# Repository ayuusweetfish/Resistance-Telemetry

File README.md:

# Resistance Telemetry

*🚧 Feature complete. Docs to be polished.*

A compact sensor for a variable resistance that transmits data through BLE. A client program provides an interface for plotting and inspecting values on a desktop computer.

The device is physically compact (3.3 cm × 1.7 cm, around the size of the battery cell plus the antenna). It is powered by a LIR2016 cell and requires no setup on the computer side. Resolution is 24-bit, but no extensive calibration has currently been carried out. Designed for laboratory use, e.g. for e-skin gloves user studies.

## Directory structure

- **hardware/**: Circuit board design files.
- **firmware/**: Firmware (PlatformIO / C).
- **client/**: The client in C++. A Windows build is automated through [GitHub Actions](https://github.com/ayuusweetfish/Resistance-Telemetry/actions).
- **misc/**: Miscellaneous files and backups.
  - **STM32F1_test1/**: Test BLE transmission on a [blue pill](https://stm32-base.org/boards/STM32F103C8T6-Blue-Pill.html) board.
  - **compress_24b.c**: Data compression through least-squares quadratic fitting. Not employed in the final version due to nonnecessity for further enhancement.

## Permit

All content in this repository is released under [CC BY-NC-SA 4.0](https://creativecommons.org/licenses/by-nc-sa/4.0/). Additionally, software source code is dual-licensed by [Hippocratic License 2.1](https://spdx.org/licenses/Hippocratic-2.1.html).

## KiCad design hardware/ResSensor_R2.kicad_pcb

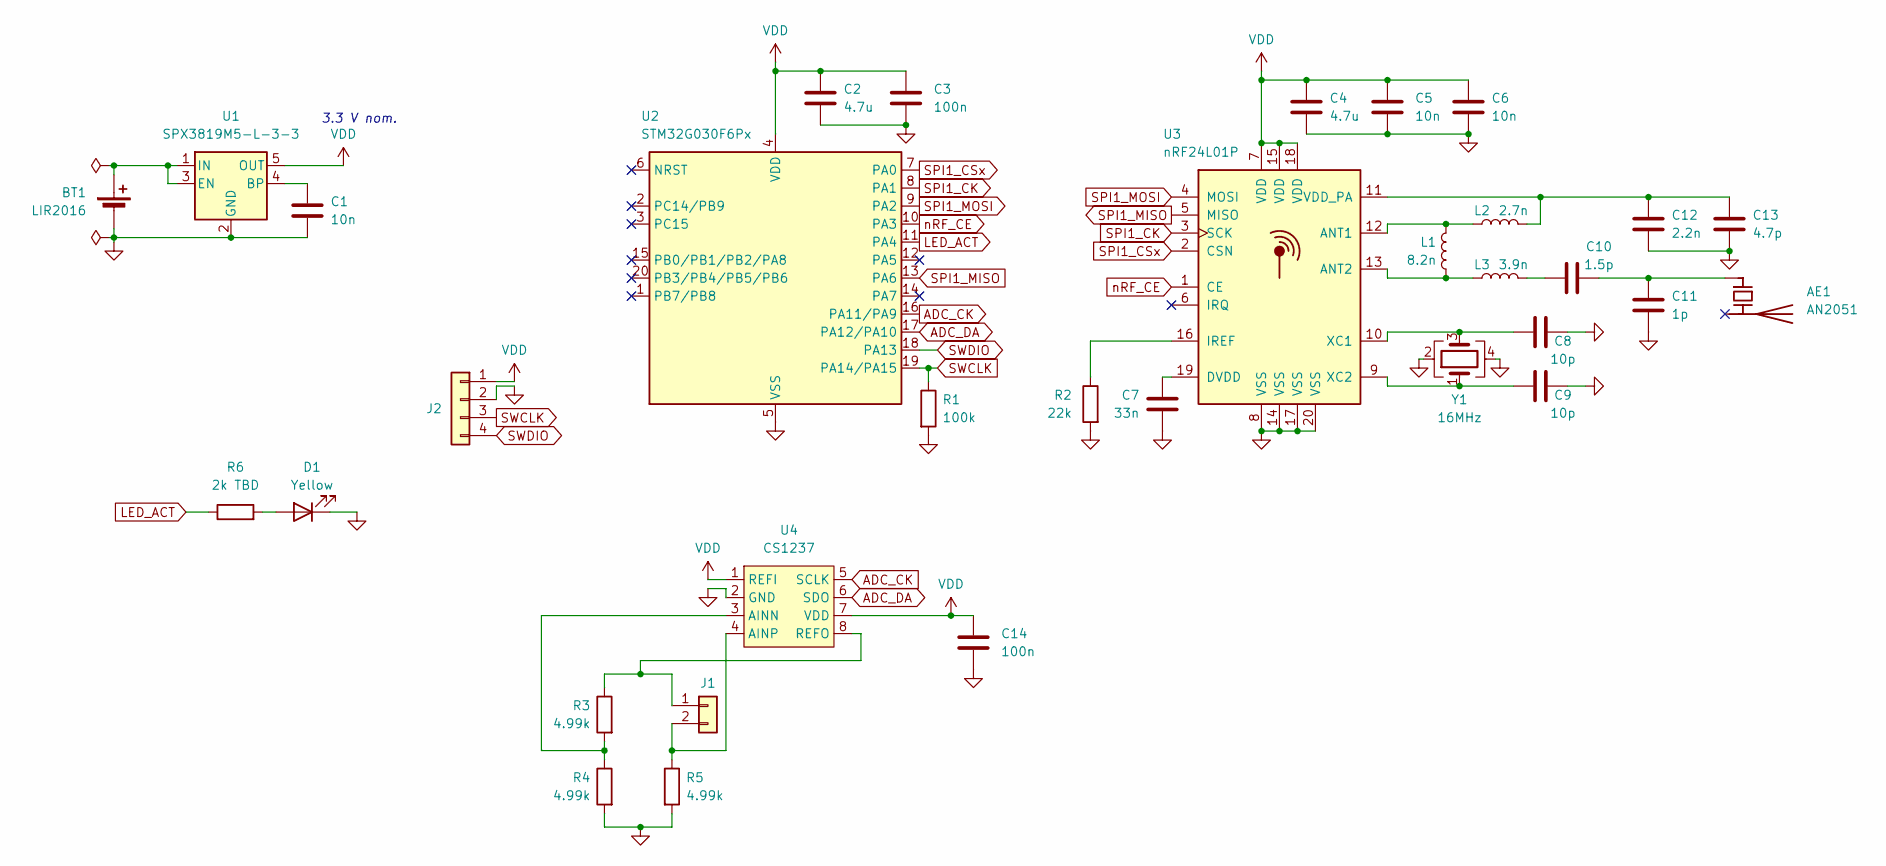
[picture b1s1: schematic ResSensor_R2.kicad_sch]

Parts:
AE1: AN2051; ANTC5020X127N
BT1: LIR2016; BatteryHolder_2032_THT_P20
C1: 10n; C_0603_1608Metric
C2, C4: 4.7u; C_0603_1608Metric
C3, C14: 100n; C_0603_1608Metric
C5, C6: 10n; C_0402_1005Metric
C7: 33n; C_0402_1005Metric
C8, C9: 10p; C_0402_1005Metric
C10: 1.5p; C_0402_1005Metric
C11: 1p; C_0402_1005Metric
C12: 2.2n; C_0402_1005Metric
C13: 4.7p; C_0402_1005Metric
D1: Yellow; LED_0603_1608Metric
J1: Conn_01x02; JST_GH_SM02B-GHS-TB_1x02-1MP_P1.25mm_Horizontal
J2: Conn_01x04; TestPoints_1x04_P2.0
L1: 8.2n; C_0402_1005Metric
L2: 2.7n; C_0402_1005Metric
L3: 3.9n; C_0402_1005Metric
R1: 100k; R_0603_1608Metric
R2: 22k; R_0603_1608Metric
R3, R4, R5: 4.99k; R_0603_1608Metric
R6: 2k TBD; R_0603_1608Metric
U1: SPX3819M5-L-3-3; SOT-23-5
U2: STM32G030F6Px; TSSOP-20_4.4x6.5mm_P0.65mm
U3: nRF24L01P; QFN-20-P0.5
U4: CS1237; SOP-8_3.76x4.96mm_P1.27mm
Y1: 16MHz; Crystal_SMD_2016-4Pin_2.0x1.6mm

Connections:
ADC_CK: U2.16 (PA11/PA9), U4.5 (SCLK)
ADC_DA: U2.17 (PA12/PA10), U4.6 (SDO)
GND: BT1.2 (-), C1.2, C2.2, C3.2, C4.2, C5.2, C6.2, C7.2, C8.2, C9.2, C11.2, C12.2, C13.2, C14.2, D1.1 (K), J2.2, R1.2, R2.2, R4.2, R5.2, U1.2 (GND), U2.5 (VSS), U3.8 (VSS), U3.14 (VSS), U3.17 (VSS), U3.20 (VSS), U4.2 (GND), Y1.2, Y1.4
LED_ACT: R6.1, U2.11 (PA4)
unnamed: AE1.1 (FEED), C10.2, C11.1
unnamed: BT1.1 (+), U1.1 (IN), U1.3 (EN)
unnamed: C10.1, L3.2
unnamed: D1.2 (A), R6.2
unnamed: J1.1, R3.1, U4.8 (REFO)
unnamed: J1.2, R5.1, U4.4 (AINP)
unnamed: C1.1, U1.4 (BP)
unnamed: L1.1, L2.1, U3.12 (ANT1)
unnamed: L1.2, L3.1, U3.13 (ANT2)
unnamed: C7.1, U3.19 (DVDD)
unnamed: R2.1, U3.16 (IREF)
unnamed: C12.1, C13.1, L2.2, U3.11 (VDD_PA)
unnamed: C8.1, U3.10 (XC1), Y1.3
unnamed: C9.1, U3.9 (XC2), Y1.1
unnamed: R3.2, R4.1, U4.3 (AINN)
SPI1_CK: U2.8 (PA1), U3.3 (SCK)
SPI1_CSx: U2.7 (PA0), U3.2 (CSN)
SPI1_MISO: U2.13 (PA6), U3.5 (MISO)
SPI1_MOSI: U2.9 (PA2), U3.4 (MOSI)
SWCLK: J2.3, R1.1, U2.19 (PA14/PA15)
SWDIO: J2.4, U2.18 (PA13)
VDD: C2.1, C3.1, C4.1, C5.1, C6.1, C14.1, J2.1, U1.5 (OUT), U2.4 (VDD), U3.7 (VDD), U3.15 (VDD), U3.18 (VDD), U4.1 (REFI), U4.7 (VDD)
nRF_CE: U2.10 (PA3), U3.1 (CE)

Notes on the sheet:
3.3 V nom.

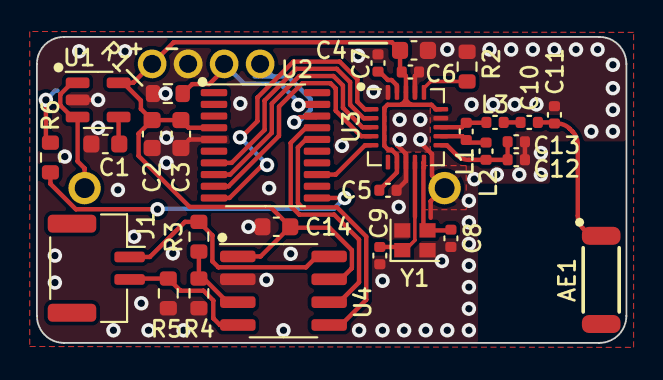
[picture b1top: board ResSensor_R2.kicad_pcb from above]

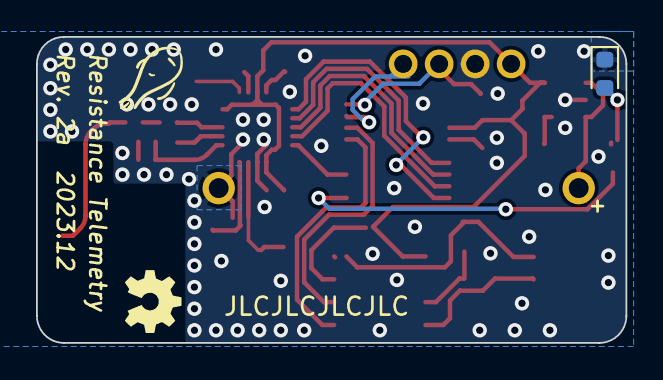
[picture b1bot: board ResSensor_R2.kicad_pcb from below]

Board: 2 copper layers, 32.8 x 17.0 mm, 33 parts (2 on the bottom side), 27 nets.

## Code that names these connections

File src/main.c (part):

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  }
}

#define PIN_ADC_CK  GPIO_PIN_11
#define PIN_ADC_DA  GPIO_PIN_12
void adc_configure();

SPI_HandleTypeDef spi1 = { 0 };
#define PIN_nRF_CS  GPIO_PIN_0
#define PIN_nRF_CE  GPIO_PIN_3

static inline void nRF_send_len(const uint8_t *cmd, uint32_t size)
{
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  HAL_GPIO_Init(LED_PORT, &gpio_init);
  HAL_GPIO_WritePin(LED_PORT, LED_PIN_ACT, GPIO_PIN_RESET);

  // SWD (PA13, PA14)
  gpio_init.Pin = GPIO_PIN_13 | GPIO_PIN_14;
  gpio_init.Mode = GPIO_MODE_AF_PP; // Pass over control to AF peripheral
  gpio_init.Alternate = GPIO_AF0_SWJ;
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
  HAL_NVIC_SetPriority(SysTick_IRQn, 0, 0);

  HAL_GPIO_WritePin(GPIOA, PIN_ADC_CK, GPIO_PIN_SET);

  // ======== SPIx ADC ========
  // ADC_CK
  gpio_init.Pin = PIN_ADC_CK;
  gpio_init.Mode = GPIO_MODE_OUTPUT_PP;
  gpio_init.Pull = GPIO_NOPULL;
  gpio_init.Speed = GPIO_SPEED_FREQ_HIGH;
  HAL_GPIO_Init(GPIOA, &gpio_init);
  // ADC_DA
  gpio_init.Pin = PIN_ADC_DA;
  gpio_init.Mode = GPIO_MODE_INPUT;
  gpio_init.Pull = GPIO_NOPULL;
  gpio_init.Speed = GPIO_SPEED_FREQ_HIGH;
  HAL_GPIO_Init(GPIOA, &gpio_init);

  HAL_GPIO_WritePin(GPIOA, PIN_ADC_CK, GPIO_PIN_RESET);
  HAL_Delay(1);
  while (HAL_GPIO_ReadPin(GPIOA, PIN_ADC_DA) == GPIO_PIN_SET) { }
  adc_configure();

  // PA12 - EXTI line 12
/*
  HAL_NVIC_SetPriority(EXTI4_15_IRQn, 2, 0);
  HAL_NVIC_EnableIRQ(EXTI4_15_IRQn);
*/

  // Pull down clock / chip select signal and wait for DRDY
  HAL_GPIO_WritePin(GPIOA, PIN_ADC_CK, GPIO_PIN_RESET);

  // ======== SPI ========
  // GPIO ports
  // SPI1_SCK (PA1), SPI1_MOSI (PA2), SPI1_MISO (PA6)
  gpio_init.Pin = GPIO_PIN_1 | GPIO_PIN_2 | GPIO_PIN_6;
  gpio_init.Mode = GPIO_MODE_AF_PP;
  gpio_init.Alternate = GPIO_AF0_SPI1;
  gpio_init.Pull = GPIO_NOPULL;
  gpio_init.Speed = GPIO_SPEED_FREQ_HIGH;
  HAL_GPIO_Init(GPIOA, &gpio_init);
  // nRF24L01+ CSN (PA0)
  gpio_init.Mode = GPIO_MODE_OUTPUT_PP;
  gpio_init.Pin = PIN_nRF_CS | PIN_nRF_CE;
  HAL_GPIO_Init(GPIOA, &gpio_init);
  HAL_GPIO_WritePin(GPIOA, PIN_nRF_CS, GPIO_PIN_SET);
  HAL_GPIO_WritePin(GPIOA, PIN_nRF_CE, GPIO_PIN_RESET);

  __HAL_RCC_SPI1_CLK_ENABLE();
  spi1.Instance = SPI1;
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    nRF_send(0xE2); // FLUSH_RX
    nRF_cmd_buf[0] = 0xA0;  // W_TX_PAYLOAD
    nRF_send_len(nRF_cmd_buf, p + 4);
    HAL_GPIO_WritePin(GPIOA, PIN_nRF_CE, GPIO_PIN_SET);
    /* while (1) {
      HAL_GPIO_WritePin(GPIOA, PIN_nRF_CS, GPIO_PIN_RESET);
      uint8_t spi_tx[1] = {0xFF};
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      HAL_Delay(1);
    } */
    HAL_Delay(20);
    HAL_GPIO_WritePin(GPIOA, PIN_nRF_CE, GPIO_PIN_RESET);
  }

  while (true) {
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inline void adc_configure()
{
  GPIO_InitTypeDef gpio_init;
  gpio_init.Pin = PIN_ADC_DA;
  gpio_init.Pull = GPIO_NOPULL;
  gpio_init.Speed = GPIO_SPEED_FREQ_HIGH;

  HAL_GPIO_WritePin(GPIOA, PIN_ADC_CK, GPIO_PIN_RESET);
  adc_ser_delay();
  for (int i = 0; i < 29; i++) {
    HAL_GPIO_WritePin(GPIOA, PIN_ADC_CK, GPIO_PIN_SET);
    adc_ser_delay();
    HAL_GPIO_WritePin(GPIOA, PIN_ADC_CK, GPIO_PIN_RESET);
    adc_ser_delay();
  }

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  HAL_GPIO_Init(GPIOA, &gpio_init);
  uint8_t writes[2] = {0x65 << 1, 0b00010100};
  for (int i = 0; i < 16; i++) {
    HAL_GPIO_WritePin(GPIOA, PIN_ADC_CK, GPIO_PIN_SET);
    HAL_GPIO_WritePin(GPIOA, PIN_ADC_DA, (writes[i / 8] >> (7 - i % 8)) & 1);
    adc_ser_delay();
    HAL_GPIO_WritePin(GPIOA, PIN_ADC_CK, GPIO_PIN_RESET);
    adc_ser_delay();
  }

  gpio_init.Mode = GPIO_MODE_IT_FALLING;
  HAL_GPIO_Init(GPIOA, &gpio_init);
  HAL_GPIO_WritePin(GPIOA, PIN_ADC_CK, GPIO_PIN_SET);
  adc_ser_delay();
  HAL_GPIO_WritePin(GPIOA, PIN_ADC_CK, GPIO_PIN_RESET);
  adc_ser_delay();
}

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{
  uint32_t value = 0;
  for (int i = 0; i < 24; i++) {
    HAL_GPIO_WritePin(GPIOA, PIN_ADC_CK, GPIO_PIN_SET);
    adc_ser_delay();
    uint32_t bit = HAL_GPIO_ReadPin(GPIOA, PIN_ADC_DA);
    value = (value << 1) | bit;
    HAL_GPIO_WritePin(GPIOA, PIN_ADC_CK, GPIO_PIN_RESET);
    adc_ser_delay();
  }
  return value;
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        swv_printf("[%02d] = %06x\n", i, ticks[i]);
      }
  }
  __HAL_GPIO_EXTI_CLEAR_FALLING_IT(PIN_ADC_DA);
}

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
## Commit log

2023-11-21 🎉 Initial commit, building for STM32G030
2023-11-24 Blinking pin
2023-11-24 Test DRDY signal of ADC
2023-11-25 Interrupt by DRDY
2023-11-25 Read out ADC
2023-11-25 Configure ADC PGA and sample rate
2023-11-25 SPI communication with nRF24L01+
2023-11-27 Set up nRF24L01+
2023-11-27 WIP: nRF24L01+ BLE
2023-12-01 Add STM32F1 test
2023-12-01 Copy existing program to test bench
2023-12-01 Fix program bugs; working BTLE advertisement
2023-12-02 Add user data in BLE
2023-12-04 (WIP) Port RF payload fixes back to the device
2023-12-05 Larger payload size in advertisement
2023-12-05 Create C++ client
2023-12-08 Transmit real data to computer
2023-12-09 Sort-out; add hardware design files
2023-12-09 Change ADC sampling rate back to 10 Hz
2023-12-09 Calculate resistance values
2023-12-16 Revise hardware, adding indicator LED
2024-01-07 Start HTTP server in C++
2024-01-07 Plot data on web page
2024-01-07 Add switch to read HTML file rather than compile-in
    For faster iteration cycles during development
2024-01-07 Update plot with data on the server
2024-01-09 Incorporate SVD subroutine
2024-01-09 Correctly calculate pseudoinverse
2024-01-09 Predict values through LLS-fit coefficients
2024-01-09 Clean ups (ref. EISPACK)
2024-01-10 Fix ADC may not be correctly initialized
2024-01-10 Update firmware with blinking LED
2024-01-10 Breathing LED
2024-01-10 Spread past values in data transmission
2024-01-10 Transmit and receive all 5 data samples
2024-01-10 Change device name and address; prepare for shipping
2024-01-10 Detect power supply level and issue warnings for low VDD
2024-01-10 Enter sleep mode during delays
    Also, revert on-chip ADC due to timing issues (see notes in code)
2024-01-10 Display real data on the web page!
2024-01-10 Further reduce clock frequencies
2024-01-11 Handle device resets & continuations in client
2024-01-11 Add clear/pause/resume functionalities
2024-01-11 Miscellaneous fixes and improvements
2024-01-11 Launch browser on client startup
2024-01-11 Wait for key before quitting on errors
2024-01-11 Various clean-ups and sort-outs
2024-01-15 GitHub Workflow testrun
2024-01-15 Squashed commit of the following:
    commit bfc24bf3c2b075074b0a3f08a46caad597bdf8d0
    Author: Ayu <claire@ayu.land>
    Date: Mon Jan 15 23:48:35 2024 +0800
    +
    commit 773cda7dd36e343359717d87144b396bbcf3ec95
    Author: Ayu <claire@ayu.land>
2024-01-15 [ci skip] Revert workflow trigger to only at client code change
2024-01-15 Reorganise files and add README
